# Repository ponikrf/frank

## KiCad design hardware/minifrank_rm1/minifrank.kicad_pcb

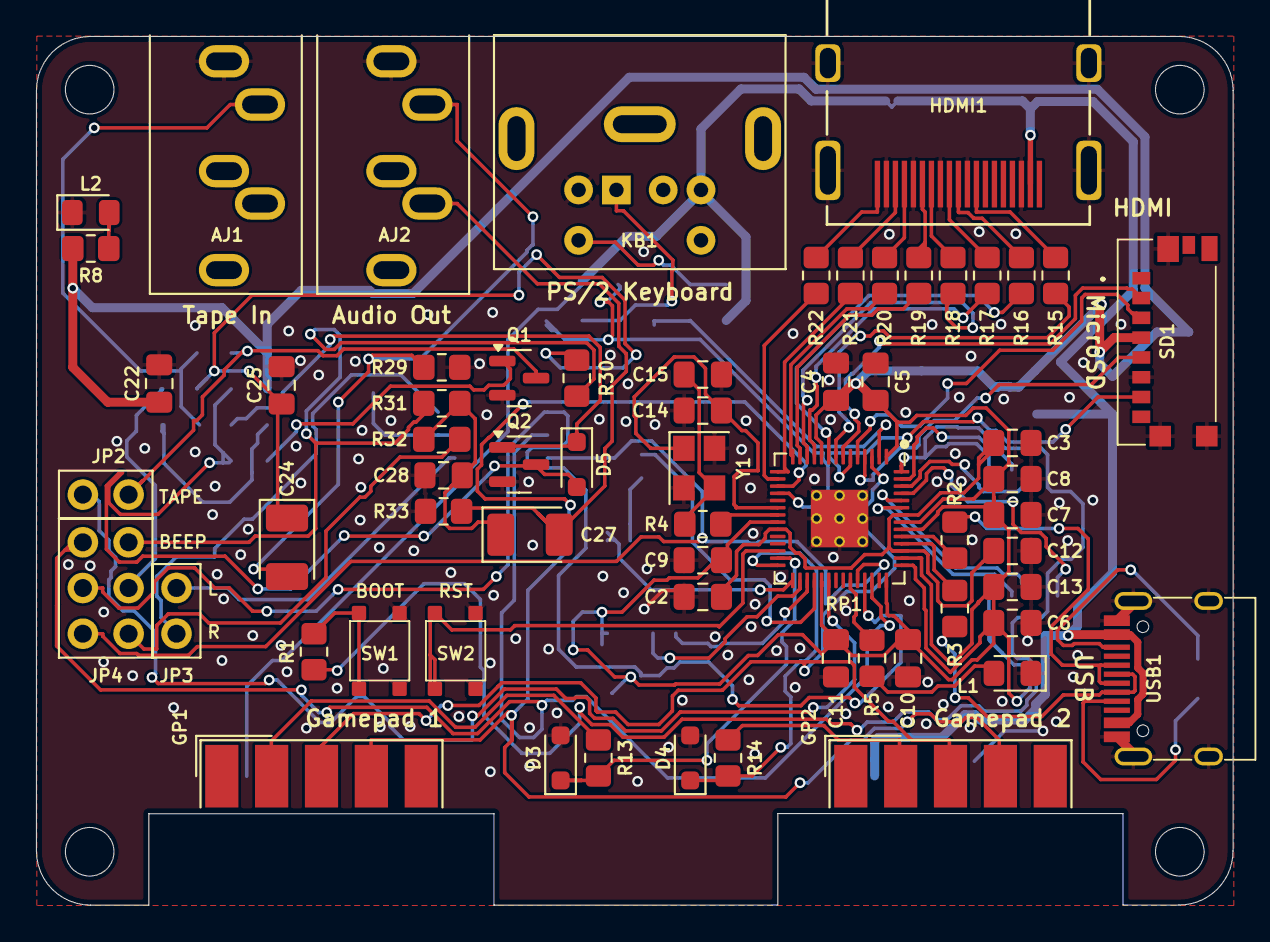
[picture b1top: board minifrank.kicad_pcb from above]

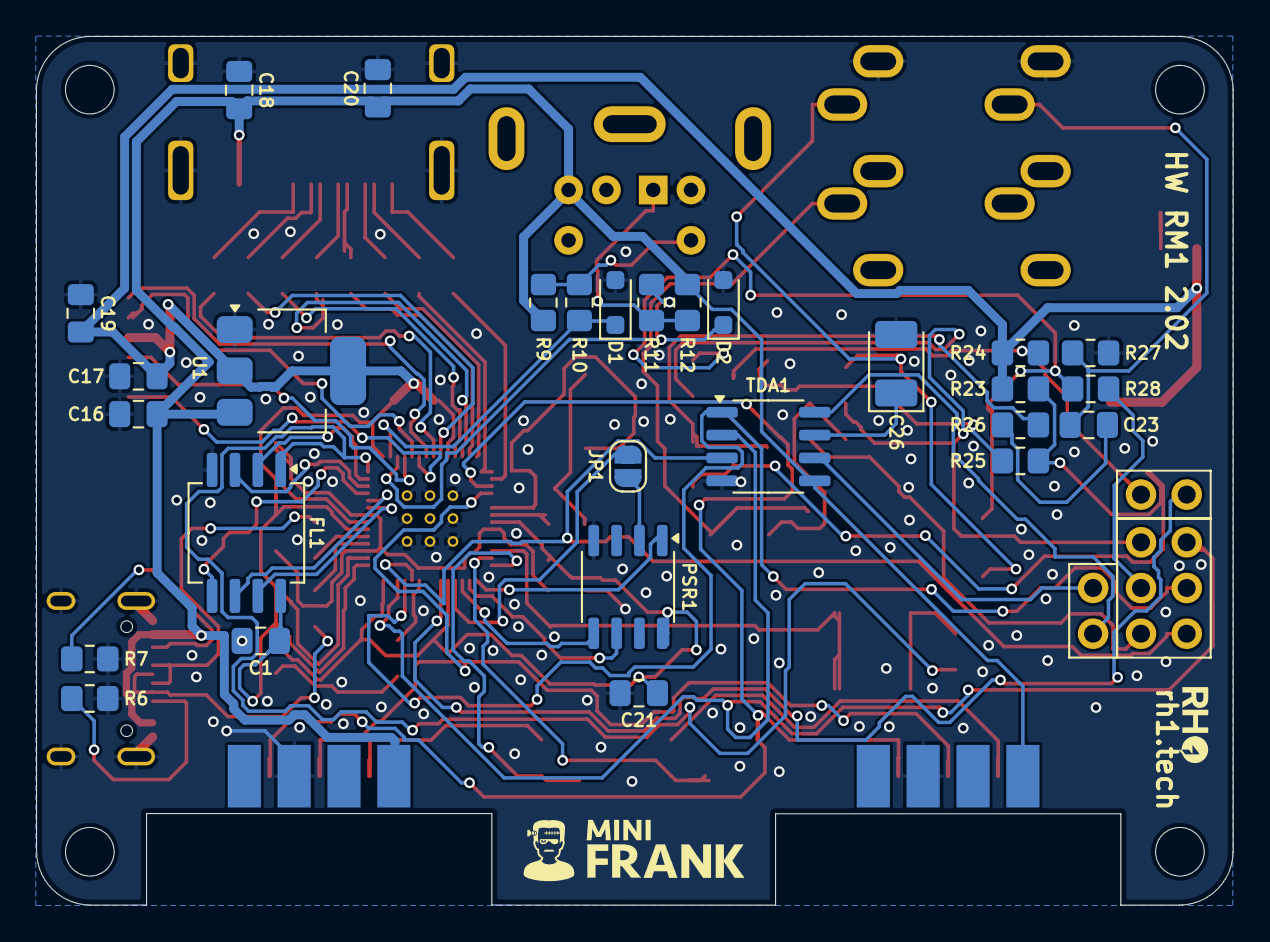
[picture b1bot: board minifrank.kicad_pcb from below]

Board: 2 copper layers, 66.5 x 48.3 mm, 94 parts (28 on the bottom side), 79 nets.

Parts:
AJ1: Audio In; Jack (3.5mm)
AJ2: Audio Out; Jack (3.5mm)
C1, C2, C3, C4, C5, C6, C7, C8, C9, C10, C11, C18, C19, C20, C21, C22, C23: 100n; Capacitor (0805)
C12, C13: 1u; Capacitor (0805)
C14, C15: 15p; Capacitor (0805)
C16, C17: 10u; Capacitor (0805)
C24, C26, C27: 10u*; Capacitor (3528, tantalum, polar)
C25, C28: 10n; Capacitor (0805)
D1, D2, D3, D4: 3V3; Diode (SOD-323)
D5: 1N4148; Diode (SOD-323)
FL1: W25Q128JVSIQ; SOIC-8
GP1, GP2: Gamepad; D-SUB (9 pin, male)
H1, H2, H3, H4: MountingHole; Mounting Hole (2.7mm)
HDMI1: HDMI Female; HDMI (female)
JP1: Jumper PSRAM (2.54); Jumper (solder)
JP2: Jumper Tape In(2.54); Pin Header (1x02)
JP3: Jumper I2S(2.54); Pin Header (1x02)
JP4: Jumpers Audio(2.54); Pin Header (2x03)
KB1: PS/2 Keyboard; MiniDIN (6 Pin, female)
L1: BLUE; LED (0805)
L2: GREEN; LED (0805)
PSR1: ESP-PSRAM32; SO-8
Q1, Q2: BC850; SOT-23
R1, R4, R5, R8, R9, R12, R13, R14, R24, R28, R32: 1K; Resistor (0805)
R2, R3: 27R; Resistor (0805)
R6, R7: 5.1K; Resistor (0805)
R10, R11, R27: 100R; Resistor (0805)
R15, R16, R17, R18, R19, R20, R21, R22: 270R; Resistor (0805)
R23, R25, R26: 10K; Resistor (0805)
R29, R33: 330R; Resistor (0805)
R30, R31: 2K; Resistor (0805)
RP1: RP2040; QFN 56
SD1: 47571-0001; MicroSD (SMD, short)
SW1: Flash Button; Button (SMD, 3x3mm)
SW2: Reset Button; Button (SMD, 3x3mm)
TDA1: TDA1387T; SO-8
U1: NCP1117 3.3; SOT-223
USB1: USB Type C
Y1: 12 MHz; Crystal (3225)

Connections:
+3V3: C1.1, C4.1, C5.1, C6.1, C7.1, C8.1, C9.1, C10.1, C11.1, C13.1, C17.1, C19.2, C21.1, C22.1, FL1.8 (VCC), PSR1.8 (VCC), R8.2, R23.1, R24.1, RP1.1 (IOVDD), RP1.10 (IOVDD), RP1.22 (IOVDD), RP1.33 (IOVDD), RP1.42 (IOVDD), RP1.43 (ADC_AVDD), RP1.44 (VREG_IN), RP1.48 (USB_VDD), RP1.49 (IOVDD), SD1.P4 (VDD), U1.2 (VO)
/AUDIO_B: JP4.6, RP1.40 (GPIO28_ADC2), TDA1.2 (LRCK)
/AUDIO_L: JP4.4, RP1.39 (GPIO27_ADC1), TDA1.1 (SCLK)
/AUDIO_R: JP4.2, RP1.38 (GPIO26_ADC0), TDA1.3 (DATA)
/Audio Out/BEEP_OUT: JP4.5, R30.2, R31.2
/Audio Out/FLT: C26.1, TDA1.7 (FLT)
/Audio Out/L: AJ2.T, C24.2, R29.1
/Audio Out/LEFT_OUT: JP4.3, R28.2
/Audio Out/LEFT_TDA: JP3.2, TDA1.6 (A_LEFT)
/Audio Out/R: AJ2.R, C27.2, R33.1
/Audio Out/RIGHT_OUT: JP4.1, R32.2
/Audio Out/RIGHT_TDA: JP3.1, TDA1.8 (A_RIGHT)
/D+: R2.1, USB1.6 (DP1), USB1.8 (DP2)
/D-: R3.1, USB1.5 (DN2), USB1.7 (DN1)
/GP1_DATA: D3.1 (K), R13.1, RP1.27 (GPIO16)
/GP2_DATA: D4.1 (K), R14.1, RP1.28 (GPIO17)
/GP_J3: GP1.3, GP2.3, RP1.18 (GPIO15)
/GP_J4: GP1.4, GP2.4, RP1.17 (GPIO14)
/HDMI_CLKN: R15.2, RP1.8 (GPIO6)
/HDMI_CLKP: R16.2, RP1.9 (GPIO7)
/HDMI_D0N: R17.2, RP1.11 (GPIO8)
/HDMI_D0P: R18.2, RP1.12 (GPIO9)
/HDMI_D1N: R19.2, RP1.13 (GPIO10)
/HDMI_D1P: R20.2, RP1.14 (GPIO11)
/HDMI_D2N: R21.2, RP1.15 (GPIO12)
/HDMI_D2P: R22.2, RP1.16 (GPIO13)
/LOAD_IN_D: JP2.2, RP1.34 (GPIO22)
/PS2_CLK: D1.1 (K), R10.2, RP1.2 (GPIO0)
/PS2_DATA: D2.1 (K), R11.2, RP1.3 (GPIO1)
/PSR_CE: PSR1.1 (~CE), RP1.29 (GPIO18)
/PSR_SCLK: PSR1.6 (SCLK), RP1.30 (GPIO19)
/PSR_SISIO: PSR1.5 (SI/SIO), RP1.31 (GPIO20)
/PSR_SOSIO: JP1.2 (B), RP1.32 (GPIO21)
/RP2040/GPIO25: R5.2, RP1.37 (GPIO25)
/RP2040/QSPI_SCLK: FL1.6 (CLK), RP1.52 (QSPI_SCLK)
/RP2040/QSPI_SD0: FL1.5 (DI(IO0)), RP1.53 (QSPI_SD0)
/RP2040/QSPI_SD1: FL1.2 (DO(IO1)), RP1.55 (QSPI_SD1)
/RP2040/QSPI_SD2: FL1.3 (IO2), RP1.54 (QSPI_SD2)
/RP2040/QSPI_SD3: FL1.7 (IO3), RP1.51 (QSPI_SD3)
/RP2040/QSPI_SS: FL1.1 (~CS), R1.1, RP1.56 (QSPI_SS)
/RP2040/XIN: C14.1, RP1.20 (XIN), Y1.1
/RP2040/XOUT: R4.1, RP1.21 (XOUT)
/RP2040/~USB_BOOT: R1.2, SW1.3, SW1.4
/RUN: RP1.26 (RUN), SW2.3, SW2.4
/SD_CLK: RP1.4 (GPIO2), SD1.P5 (CLK)
/SD_CMD: RP1.5 (GPIO3), SD1.P3 (CMD)
/SD_DAT0: RP1.6 (GPIO4), SD1.P7 (DAT0)
/SD_DAT3: RP1.7 (GPIO5), SD1.P2 (CD/DAT3)
/Tape In/LOAD_IN_D: JP2.1, Q1.3 (C), R24.2
GND: AJ1.S, AJ2.S, C1.2, C2.2, C3.2, C4.2, C5.2, C6.2, C7.2, C8.2, C9.2, C10.2, C11.2, C12.2, C13.2, C14.2, C15.2, C16.2, C17.2, C18.2, C19.1, C20.2, C21.2, C22.2, C25.2, C26.2, C28.2, D1.2 (A), D2.2 (A), D3.2 (A), D4.2 (A), FL1.4 (GND), GP1.8, GP2.8, HDMI1.2 (G_D2), HDMI1.5 (G_D1), HDMI1.8 (G_D0), HDMI1.11 (G_CLK), HDMI1.17 (G_DDC/CEC), HDMI1.20 (SHIELD1), HDMI1.21 (SHIELD2), HDMI1.22 (SHIELD3), HDMI1.23 (SHIELD4), KB1.3, L1.1 (K), L2.1 (K), PSR1.4 (VSS), Q1.2 (E), Q2.2 (E), R6.1, R7.1, R27.2, R29.2, R33.2, RP1.19 (TESTEN), RP1.57 (GND), SD1.G1 (GND_1), SD1.G2 (GND_2), SD1.G3 (GND_3), SD1.P6 (VSS), SW1.1, SW1.2, SW2.1, SW2.2, TDA1.4 (AGND), U1.1 (GND), USB1.1 (GND), USB1.12 (GND), USB1.13 (SHIELD), Y1.2, Y1.4
unnamed: AJ1.T, C23.1, R27.1
unnamed: C15.1, R4.2, Y1.3
unnamed: C23.2, R26.1
unnamed: C24.1, C25.1, R28.1, R30.1
unnamed: C27.1, C28.1, R31.1, R32.1
unnamed: D5.2 (A), Q2.3 (C), R23.2, R25.1
unnamed: D5.1 (K), Q2.1 (B), R26.2
unnamed: GP1.2, R13.2
unnamed: GP2.2, R14.2
unnamed: HDMI1.12 (CLKN), R15.1
unnamed: HDMI1.10 (CLKP), R16.1
unnamed: HDMI1.9 (D0N), R17.1
unnamed: HDMI1.7 (D0P), R18.1
unnamed: HDMI1.6 (D1N), R19.1
unnamed: HDMI1.4 (D1P), R20.1
unnamed: HDMI1.3 (D2N), R21.1
unnamed: HDMI1.1 (D2P), R22.1
unnamed: JP1.1 (A), PSR1.2 (SO/SIO)
unnamed: KB1.1, R11.1, R12.2
unnamed: KB1.5, R9.2, R10.1
unnamed: L1.2 (A), R5.1
unnamed: L2.2 (A), R8.1
unnamed: Q1.1 (B), R25.2
unnamed: R3.2, RP1.46 (USB_DM)
unnamed: R2.2, RP1.47 (USB_DP)
unnamed: C2.1, C3.1, C12.1, RP1.23 (DVDD), RP1.45 (VREG_VOUT), RP1.50 (DVDD)
unnamed: R6.2, USB1.4 (CC1)
unnamed: R7.2, USB1.10 (CC2)
VBUS: C16.1, C18.1, C20.1, GP1.6, GP2.6, HDMI1.18 (+5V), KB1.4, R9.1, R12.1, TDA1.5 (VA), U1.3 (VI), USB1.2 (VBUS), USB1.11 (VBUS)

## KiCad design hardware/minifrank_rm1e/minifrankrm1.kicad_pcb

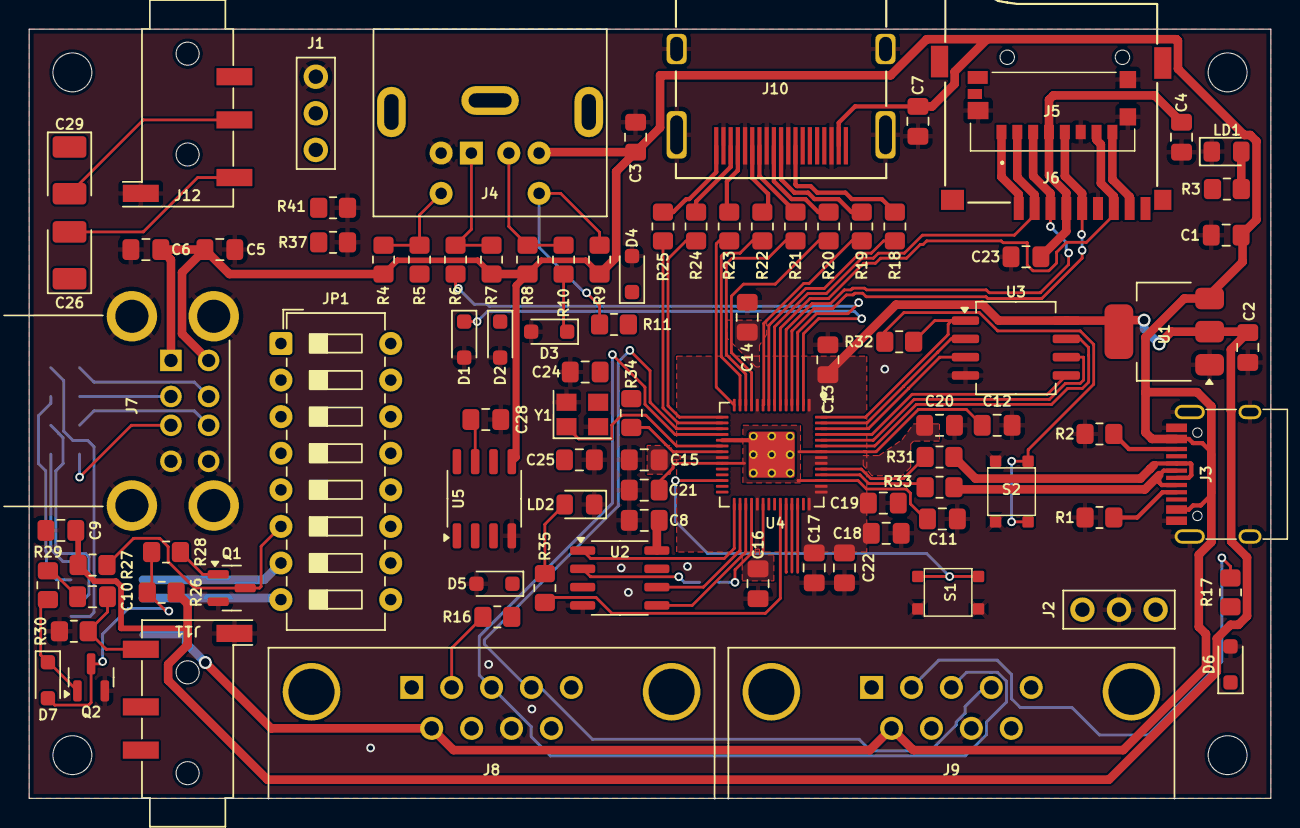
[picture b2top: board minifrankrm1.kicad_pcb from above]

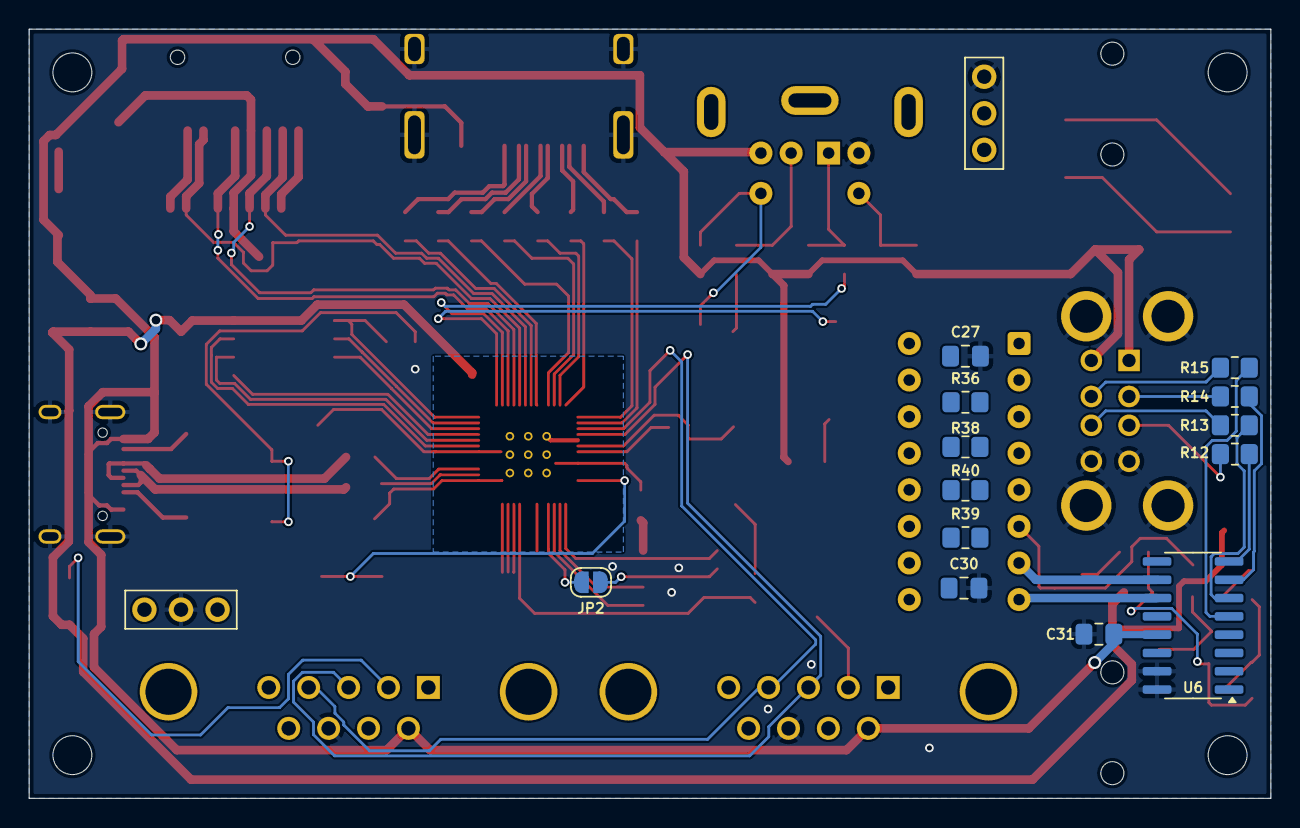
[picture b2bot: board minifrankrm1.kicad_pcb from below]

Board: 2 copper layers, 86.2 x 53.4 mm, 110 parts (13 on the bottom side), 96 nets.

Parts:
C1, C2, C5, C6, C28: 10u; Capacitor (0805)
C3, C4, C7, C8, C9, C10, C11, C12, C13, C14, C15, C16, C17, C18, C19, C20, C23: 100n; Capacitor (0805)
C21, C22: 1u; Capacitor (0805)
C24, C25: 15p; Capacitor (0805)
C26, C29: 10u; Capacitor (3528, tantalum, polar)
C27, C30: 10n; Capacitor (0805)
C31: 4.7u; Capacitor (0805)
D1, D2, D3, D4, D5, D6: 3V3; Diode (SOD-323)
D7: 1N4148; Diode (SOD-323)
H1, H2, H3, H4: Hole 2.7mm; Mounting Hole (2.7mm)
J1: UART; Pin Header (1x03)
J2: Power; Pin Header (1x03)
J3: USB4215; USB Type C
J4: MDC-036; MiniDIN (6 Pin, female)
J5: 0475710001; MicroSD (SMD, short)
J6: 104031-0811; MicroSD (SMD, long)
J7: SS-52100-004; USB Type A (stacked)
J8, J9: D-SUB 9 Male; D-SUB (9 pin, male, top mount)
J10: DC3RX19JA2; HDMI (female)
J11, J12: PJ-320D; Jack (3.5mm, PJ-320D)
JP1: Main Jumpers; DIP Switch (8x8)
JP2: Jumper (Solder); Jumper (solder)
LD1: Green; LED (0805)
LD2: Blue; LED (0805)
Q1, Q2: BC850; SOT-23
R1, R2: 5.1K; Resistor (0805)
R3, R4, R7, R8, R9, R16, R17, R27, R32, R34, R35, R36, R40: 1K; Resistor (0805)
R5, R6, R10, R11, R30: 100R; Resistor (0805)
R12, R13, R14, R15: 22R; Resistor (0805)
R18, R19, R20, R21, R22, R23, R24, R25: 270R; Resistor (0805)
R26, R28, R29: 10K; Resistor (0805)
R31, R33: 27R; Resistor (0805)
R37, R41: 330R; Resistor (0805)
R38, R39: 2K; Resistor (0805)
S1, S2: TS-1233; Button (SMD, 3x3mm, 1-1)
U1: NCP1117 3.3; SOT-223
U2: ESP-PSRAM32; SO-8
U3: W25Q128JVSIQ; SOIC-8
U4: RP2040; QFN 56
U5: TDA1387T; SO-8
U6: MW7211A; SOP-16
Y1: 12 MHz; Crystal (3225)

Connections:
+3V3: C2.1, C4.2, C8.1, C9.1, C13.1, C14.1, C15.1, C16.1, C17.1, C18.1, C19.1, C20.1, C22.1, C23.1, J2.1, J5.P4 (VDD), J6.4 (VDD), R3.2, R26.1, R27.1, U1.2 (VO), U2.8 (VCC), U3.8 (VCC), U4.1 (IOVDD), U4.10 (IOVDD), U4.22 (IOVDD), U4.33 (IOVDD), U4.42 (IOVDD), U4.43 (ADC_AVDD), U4.44 (VREG_IN), U4.48 (USB_VDD), U4.49 (IOVDD)
/Audio/L: C26.2, J12.T, R37.1
/Audio/R: C29.2, J12.R, R41.1
/GP1_DATA: D5.1 (K), R16.1
/GP2_DATA: D6.1 (K), R17.1
/GPIO0: D1.1 (K), J1.2, R5.2, U4.2 (GPIO0)
/GPIO1: D2.1 (K), J1.3, R6.2, U4.3 (GPIO1)
/GPIO2: J5.P5 (CLK), J6.5 (CLK), U4.4 (GPIO2)
/GPIO3: J5.P3 (CMD), J6.3 (CMD), U4.5 (GPIO3)
/GPIO4: J5.P7 (DAT0), J6.7 (DAT0), U4.6 (GPIO4)
/GPIO5: J5.P2 (CD/DAT3), J6.2 (DAT3/CD), U4.7 (GPIO5)
/GPIO6: R18.2, U4.8 (GPIO6)
/GPIO7: R19.2, U4.9 (GPIO7)
/GPIO8: R20.2, U4.11 (GPIO8)
/GPIO9: R21.2, U4.12 (GPIO9)
/GPIO10: R22.2, U4.13 (GPIO10)
/GPIO11: R23.2, U4.14 (GPIO11)
/GPIO12: R24.2, U4.15 (GPIO12)
/GPIO13: R25.2, U4.16 (GPIO13)
/GPIO14: J8.4, J9.4, U4.17 (GPIO14)
/GPIO15: J8.3, J9.3, U4.18 (GPIO15)
/GPIO18: U2.1 (~CE), U4.29 (GPIO18)
/GPIO19: U2.6 (SCLK), U4.30 (GPIO19)
/GPIO20: U2.5 (SI/SIO), U4.31 (GPIO20)
/GPIO21: JP2.2 (B), U4.32 (GPIO21)
/GPIO22: JP1.12, U4.34 (GPIO22)
/GPIO26: JP1.4, U4.38 (GPIO26_ADC0), U5.3 (DATA)
/GPIO27: JP1.2, U4.39 (GPIO27_ADC1), U5.1 (SCLK)
/GPIO28: JP1.10, U4.40 (GPIO28_ADC2), U5.2 (LRCK)
/KB_CLK: J4.5, R4.2, R5.1
/KB_DATA: J4.1, R6.1, R7.2
/LOAD_IN_D: JP1.11, Q1.3 (C), R27.2
/MS_CLK: J4.6, R9.2, R11.1
/MS_CLK_3V: D4.1 (K), R11.2
/MS_DATA: J4.2, R8.2, R10.1
/MS_DATA_3V: D3.1 (K), R10.2
/Micro SD/DAT1: J5.P8 (DAT1), J6.8 (DAT1)
/Micro SD/DAT2: J5.P1 (DAT2), J6.1 (DAT2)
/OUT_B: JP1.9, R38.2, R39.2
/OUT_L: JP1.1, JP1.6, R36.2
/OUT_R: JP1.3, JP1.8, R40.2
/PW_DM: J3.5 (DN2), J3.7 (DN1), JP1.14, R33.1
/PW_DP: J3.6 (DP1), J3.8 (DP2), JP1.16, R31.1
/RP2040/GPIO25: R35.2, U4.37 (GPIO25)
/RP2040/QSPI_SCLK: U3.6 (CLK), U4.52 (QSPI_SCLK)
/RP2040/QSPI_SD0: U3.5 (DI(IO0)), U4.53 (QSPI_SD0)
/RP2040/QSPI_SD1: U3.2 (DO(IO1)), U4.55 (QSPI_SD1)
/RP2040/QSPI_SD2: U3.3 (IO2), U4.54 (QSPI_SD2)
/RP2040/QSPI_SD3: U3.7 (IO3), U4.51 (QSPI_SD3)
/RP2040/QSPI_SS: R32.1, U3.1 (~CS), U4.56 (QSPI_SS)
/RP2040/XIN: C25.1, U4.20 (XIN), Y1.1
/RP2040/XOUT: R34.1, U4.21 (XOUT)
/RP2040/~USB_BOOT: R32.2, S2.2
/RUN: S1.1, U4.26 (RUN)
/TDA_L: JP1.5, U5.6 (A_LEFT)
/TDA_R: JP1.7, U5.8 (A_RIGHT)
/UH_DM1: R14.1, U6.7 (DM3)
/UH_DM2: R15.1, U6.5 (DM2)
/UH_DM_IN: JP1.13, U6.10 (DMU)
/UH_DP1: R12.1, U6.8 (DP3)
/UH_DP2: R13.1, U6.6 (DP2)
/UH_DP_IN: JP1.15, U6.11 (DPU)
GND: C1.2, C2.2, C3.2, C4.1, C5.2, C6.2, C7.2, C8.2, C9.2, C11.2, C12.2, C13.2, C14.2, C15.2, C16.2, C17.2, C18.2, C19.2, C20.2, C21.2, C22.2, C23.2, C24.2, C25.2, C27.2, C28.2, C30.2, C31.2, D1.2 (A), D2.2 (A), D3.2 (A), D4.2 (A), D5.2 (A), D6.2 (A), J1.1, J2.2, J3.1 (GND), J3.12 (GND), J3.13 (SHIELD), J4.3, J5.G1 (GND_1), J5.G2 (GND_2), J5.G3 (GND_3), J5.P6 (VSS), J6.6 (VSS), J7.4 (GND1), J7.8 (GND2), J7.9 (Shield), J8.8, J9.8, J10.2 (G_D2), J10.5 (G_D1), J10.8 (G_D0), J10.11 (G_CLK), J10.17 (G_DDC/CEC), J10.20 (SHIELD1), J10.21 (SHIELD2), J10.22 (SHIELD3), J10.23 (SHIELD4), J11.S, J12.S, LD1.1 (K), LD2.1 (K), Q1.2 (E), Q2.2 (E), R1.1, R2.1, R30.2, R37.2, R41.2, S1.2, S2.1, U1.1 (GND), U2.4 (VSS), U3.4 (GND), U4.19 (TESTEN), U4.57 (GND), U5.4 (AGND), U6.15 (GND), U6.16 (GND), Y1.2, Y1.4
unnamed: C10.1, J11.T, R30.1
unnamed: C10.2, R29.1
unnamed: C24.1, R34.2, Y1.3
unnamed: C26.1, C27.1, R36.1, R38.1
unnamed: C29.1, C30.1, R39.1, R40.1
unnamed: D7.2 (A), Q2.3 (C), R26.2, R28.1
unnamed: D7.1 (K), Q2.1 (B), R29.2
unnamed: J3.4 (CC1), R1.2
unnamed: J3.10 (CC2), R2.2
unnamed: J7.3 (D1+), R12.2
unnamed: J7.2 (D1-), R14.2
unnamed: J7.7 (D2+), R13.2
unnamed: J7.6 (D2-), R15.2
unnamed: J8.2, R16.2
unnamed: J9.2, R17.2
unnamed: J10.12 (CLKN), R18.1
unnamed: J10.10 (CLKP), R19.1
unnamed: J10.9 (D0N), R20.1
unnamed: J10.7 (D0P), R21.1
unnamed: J10.6 (D1N), R22.1
unnamed: J10.4 (D1P), R23.1
unnamed: J10.3 (D2N), R24.1
unnamed: J10.1 (D2P), R25.1
unnamed: JP2.1 (A), U2.2 (SO/SIO)
unnamed: LD1.2 (A), R3.1
unnamed: LD2.2 (A), R35.1
unnamed: Q1.1 (B), R28.2
unnamed: R33.2, U4.46 (USB_DM)
unnamed: R31.2, U4.47 (USB_DP)
unnamed: C11.1, C12.1, C21.1, U4.23 (DVDD), U4.45 (VREG_VOUT), U4.50 (DVDD)
unnamed: C28.1, U5.7 (FLT)
unnamed: U6.12 (VD33), U6.14 (VD3)
VBUS: C1.1, C3.1, C5.1, C6.1, C7.1, C31.1, J2.3, J3.2 (VBUS), J3.11 (VBUS), J4.4, J7.1 (VBUS1), J7.5 (VBUS2), J8.6, J9.6, J10.18 (+5V), R4.1, R7.1, R8.1, R9.1, U1.3 (VI), U5.5 (VA), U6.13 (VDD5)

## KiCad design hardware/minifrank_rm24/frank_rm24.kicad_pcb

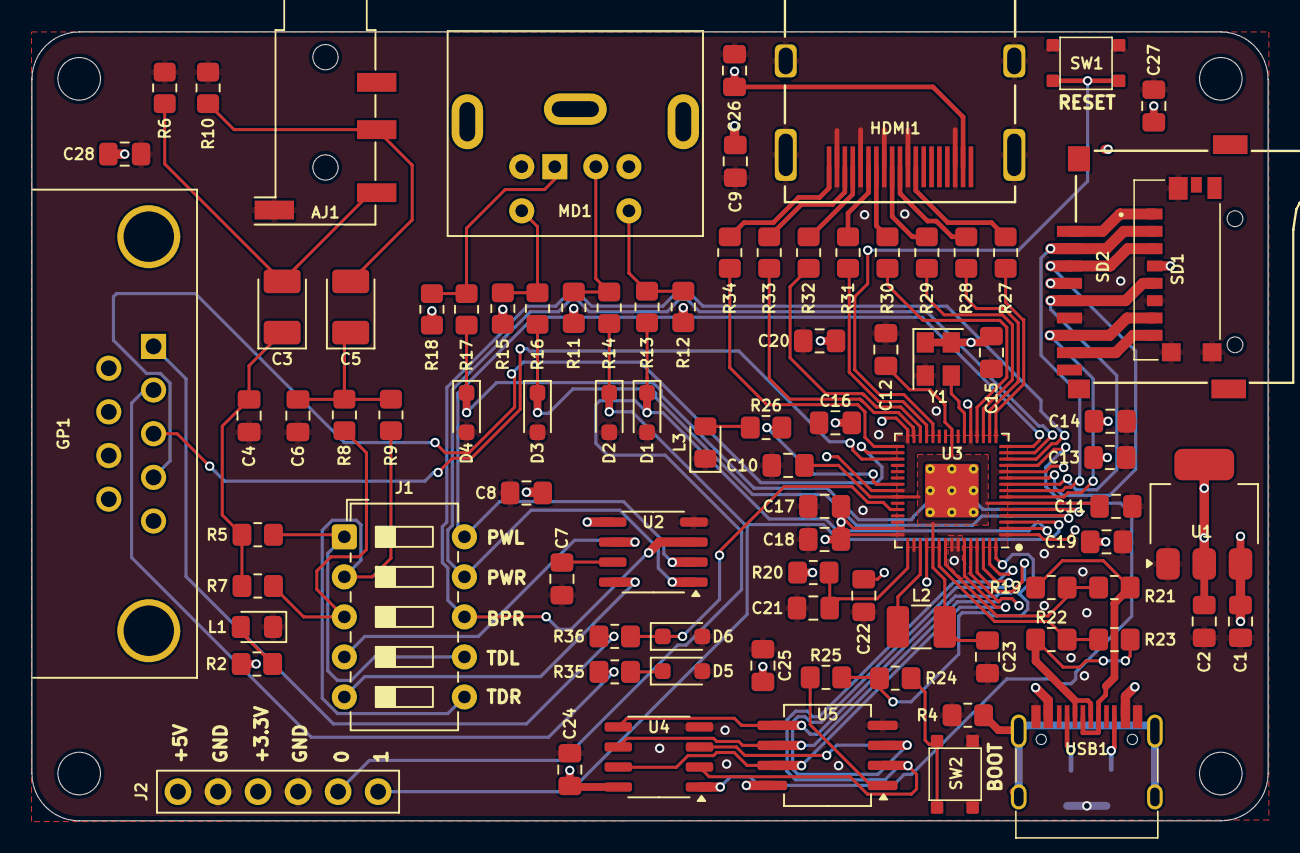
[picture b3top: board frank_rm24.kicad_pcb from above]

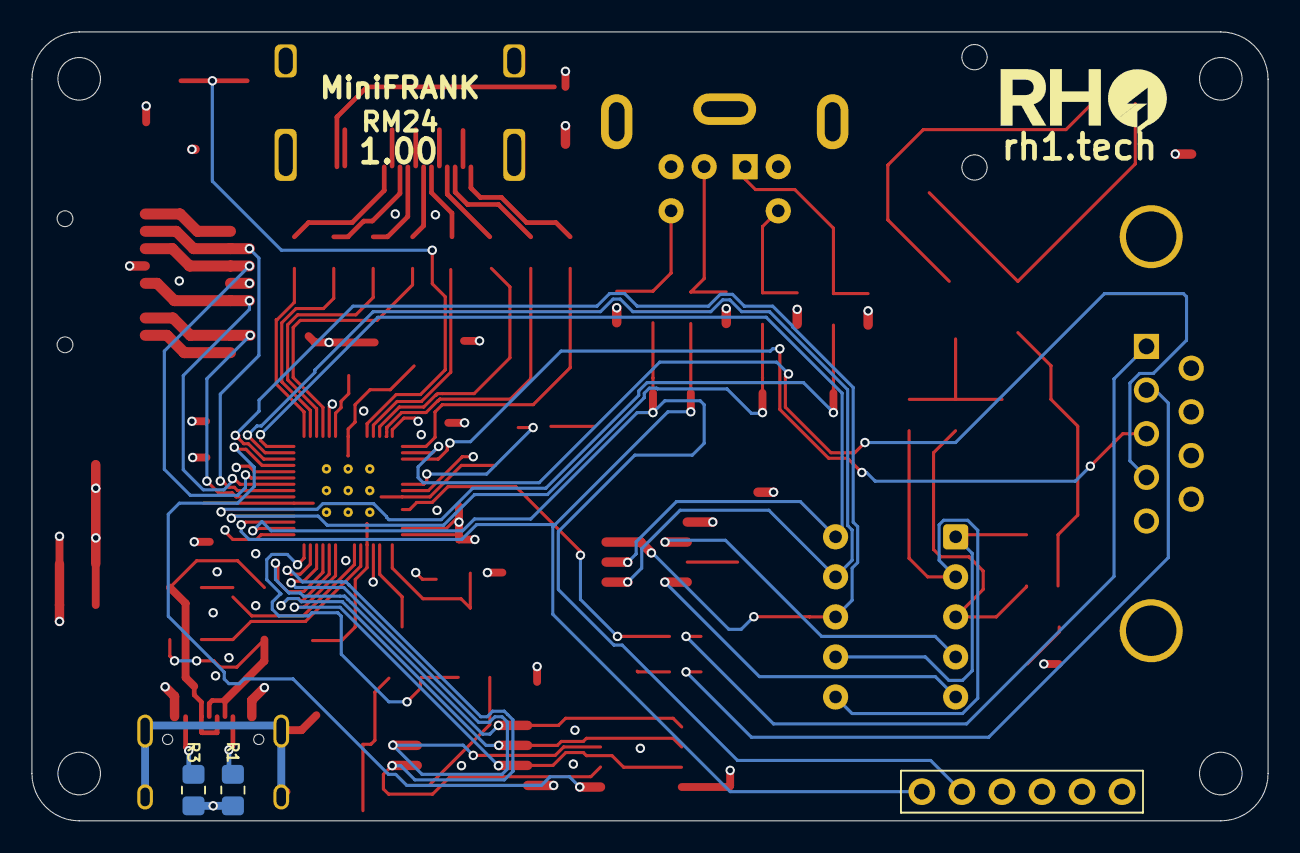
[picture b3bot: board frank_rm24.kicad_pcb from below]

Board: 4 copper layers, 78.4 x 50.0 mm, 94 parts (2 on the bottom side), 76 nets.

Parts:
AJ1: PJ-320D; Jack (3.5mm, PJ-320D)
C1, C2, C9: 10u; Capacitor (0805)
C3, C5: 10u; Capacitor (3528, tantalum, polar)
C4, C6: 10n; Capacitor (0805)
C7: 1u; Capacitor (0805)
C8: 47u; Capacitor (0805)
C10, C12, C13, C14, C15, C16, C17, C18, C19, C20, C24, C25, C26, C27, C28: 100n; Capacitor (0805)
C11, C21, C22, C23: 4.7u; Capacitor (0805)
D1, D2, D3, D4, D5, D6: 3V3; Diode (SOD-323)
GP1: Gamepad; D-SUB (9 pin, male, top mount)
H1, H2, H3, H4: MountingHole; Mounting Hole (2.7mm)
HDMI1: HDMI Female; HDMI (female)
J1: Pin Header 2x18; DIP Switch (5x5)
J2: Connectors; Pin Header (1x06)
L1: Green; LED (0805)
L2: 3.3u; Inductor (3225)
L3: Blue; LED (0805)
MD1: Mini-DIN-6; MiniDIN (6 Pin, female)
R1, R3: 5.1K; Resistor (0805)
R2, R5, R9, R11, R12, R15, R24, R26, R35, R36: 1K; Resistor (0805)
R4: 1M; Resistor (0805)
R6, R10: 330R; Resistor (0805)
R7, R8: 2K; Resistor (0805)
R13, R14, R16, R17: 100R; Resistor (0805)
R18: 1k; Resistor (0805)
R19, R22: 150R; Resistor (0805)
R20: 33; Resistor (0805)
R21, R23: 33R; Resistor (0805)
R25: 0; Resistor (0805)
R27, R28, R29, R30, R31, R32, R33, R34: 270R; Resistor (0805)
SD1: 47571-0001; MicroSD (SMD, short)
SD2: 104031-0811; MicroSD (SMD, long)
SW1: Reset; Button (SMD, 3x3mm, 1-1)
SW2: SW_Push; Button (SMD, 3x3mm, 1-1)
U1: NCP1117 3.3; SOT-223
U2: TDA1387T; SO-8
U3: RP2350_60QFN; QFN 60 (RP2350A)
U4: ESP-PSRAM32; SO-8
U5: W25Q128JVS; SOIC-8
USB1: USB4215-03-A; USB Type C
Y1: ASE-xxxMHz; Crystal (3225, active)

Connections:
+1V1: C10.1, C11.1, C12.1, C23.1, L2.1, U3.6 (DVDD), U3.23 (DVDD), U3.39 (DVDD), U3.50 (VREG_FB)
+3V3: C2.1, C13.1, C14.1, C15.1, C16.1, C17.1, C18.1, C19.1, C20.1, C22.1, C24.1, C25.1, C27.2, J2.3, R2.2, R20.1, SD1.P4 (VDD), SD2.4 (VDD), U1.2 (VO), U3.1 (IOVDD), U3.11 (IOVDD), U3.20 (IOVDD), U3.30 (IOVDD), U3.38 (IOVDD), U3.44 (ADC_AVDD), U3.45 (IOVDD), U3.49 (VREG_VIN), U3.53 (USB_OTP_VDD), U3.54 (QSPI_IOVDD), U4.8 (VCC), U5.8 (VCC), Y1.1 (EN), Y1.4 (Vdd)
/A_OUTB: J1.5, R7.2, R8.2
/A_OUTL: J1.1, J1.8, R5.2
/A_OUTR: J1.3, J1.10, R9.2
/A_TDAL: J1.7, U2.6 (A_LEFT)
/A_TDAR: J1.9, U2.8 (A_RIGHT)
/Audio Out/L: AJ1.T, C3.2, R6.1
/Audio Out/R: AJ1.R, C5.2, R10.1
/D+: R19.1, R21.1, USB1.6 (DP1), USB1.8 (DP2)
/D-: R22.1, R23.1, USB1.5 (DN2), USB1.7 (DN1)
/GPIO0: D1.1 (K), J2.5, R13.2, U3.2 (GPIO0)
/GPIO1: D2.1 (K), J2.6, R14.2, U3.3 (GPIO1)
/GPIO2: D3.1 (K), R16.2, U3.4 (GPIO2)
/GPIO3: D4.1 (K), R17.2, U3.5 (GPIO3)
/GPIO4: SD1.P7 (DAT0), SD2.7 (DAT0), U3.7 (GPIO4)
/GPIO5: SD1.P2 (CD/DAT3), SD2.2 (DAT3/CD), U3.8 (GPIO5)
/GPIO6: SD1.P5 (CLK), SD2.5 (CLK), U3.9 (GPIO6)
/GPIO7: SD1.P3 (CMD), SD2.3 (CMD), U3.10 (GPIO7)
/GPIO8: U3.12 (GPIO8), U4.1 (~CE)
/GPIO9: J1.6, U2.3 (DATA), U3.13 (GPIO9)
/GPIO10: J1.4, U2.1 (SCLK), U3.14 (GPIO10)
/GPIO11: J1.2, U2.2 (LRCK), U3.15 (GPIO11)
/GPIO12: R27.2, U3.16 (GPIO12)
/GPIO13: R28.2, U3.17 (GPIO13)
/GPIO14: R29.2, U3.18 (GPIO14)
/GPIO15: R30.2, U3.19 (GPIO15)
/GPIO16: R31.2, U3.27 (GPIO16)
/GPIO17: R32.2, U3.28 (GPIO17)
/GPIO18: R33.2, U3.29 (GPIO18)
/GPIO19: R34.2, U3.31 (GPIO19)
/GPIO20: GP1.4, U3.32 (GPIO20)
/GPIO21: GP1.3, U3.33 (GPIO21)
/GPIO26: D5.1 (K), R35.1
/GPIO27: D6.1 (K), R36.1, U3.41 (GPIO27_ADC1)
/Gamepad/J1_DATA: GP1.2, R35.2
/Gamepad/J2_DATA: GP1.1, R36.2
/PS2/PS/2 CLK: MD1.5, R15.2, R16.1
/PS2/PS/2 DATA: MD1.1, R17.1, R18.2
/RP2350A/FLASH_SS: R25.2, U5.1 (~CS)
/RP2350A/QSPI_SCLK: U3.56 (QSPI_SCLK), U4.6 (SCLK), U5.6 (CLK)
/RP2350A/QSPI_SD0: U3.57 (QSPI_SD0), U4.5 (SI/SIO), U5.5 (DI(IO0))
/RP2350A/QSPI_SD1: U3.59 (QSPI_SD1), U4.2 (SO/SIO), U5.2 (DO(IO1))
/RP2350A/QSPI_SD2: U3.58 (QSPI_SD2), U4.3 (SIO2), U5.3 (IO2)
/RP2350A/QSPI_SD3: U3.55 (QSPI_SD3), U4.7 (SIO3), U5.7 (IO3)
/RP2350A/QSPI_SS: R24.1, R25.1, U3.60 (QSPI_SS)
/RP2350A/VREG_AVDD: C21.1, R20.2, U3.46 (VREG_AVDD)
/RP2350A/VREG_LX: L2.2, U3.48 (VREG_LX)
/RP2350A/XIN: U3.21 (XIN), Y1.3 (OUT)
/RP2350A/~USB_BOOT: R24.2, SW2.2
/RUN: SW1.1, U3.26 (RUN)
/SD Card/DAT1: SD1.P8 (DAT1), SD2.8 (DAT1)
/SD Card/DAT2: SD1.P1 (DAT2), SD2.1 (DAT2)
GND: AJ1.S, C1.2, C2.2, C4.2, C6.2, C7.2, C8.1, C9.2, C10.2, C11.2, C12.2, C13.2, C14.2, C15.2, C16.2, C17.2, C18.2, C19.2, C20.2, C21.2, C22.2, C23.2, C24.2, C25.2, C26.2, C27.1, C28.2, D1.2 (A), D2.2 (A), D3.2 (A), D4.2 (A), D5.2 (A), D6.2 (A), GP1.8, HDMI1.2 (G_D2), HDMI1.5 (G_D1), HDMI1.8 (G_D0), HDMI1.11 (G_CLK), HDMI1.17 (G_DDC/CEC), HDMI1.20 (SHIELD1), HDMI1.21 (SHIELD2), HDMI1.22 (SHIELD3), HDMI1.23 (SHIELD4), J2.2, J2.4, L1.1 (K), L3.1 (K), MD1.3, R1.1, R3.1, R4.2, R6.2, R10.2, SD1.G1 (GND_1), SD1.G2 (GND_2), SD1.G3 (GND_3), SD1.P6 (VSS), SD2.6 (VSS), SW1.2, SW2.1, U1.1 (GND), U2.4 (AGND), U3.47 (VREG_PGND), U3.61 (GND), U4.4 (VSS), U5.4 (GND), USB1.1 (GND), USB1.12 (GND), Y1.2 (GND)
GPIO25: R26.2, U3.37 (GPIO25)
unnamed: C3.1, C4.1, R5.1, R7.1
unnamed: C5.1, C6.1, R8.1, R9.1
unnamed: HDMI1.12 (CLKN), R27.1
unnamed: HDMI1.10 (CLKP), R28.1
unnamed: HDMI1.9 (D0N), R29.1
unnamed: HDMI1.7 (D0P), R30.1
unnamed: HDMI1.6 (D1N), R31.1
unnamed: HDMI1.4 (D1P), R32.1
unnamed: HDMI1.3 (D2N), R33.1
unnamed: HDMI1.1 (D2P), R34.1
unnamed: L1.2 (A), R2.1
unnamed: L3.2 (A), R26.1
unnamed: MD1.2, R11.2, R14.1
unnamed: MD1.6, R12.2, R13.1
unnamed: C7.1, U2.7 (FLT)
unnamed: R22.2, R23.2, U3.51 (USB_DM)
unnamed: R19.2, R21.2, U3.52 (USB_DP)
unnamed: R1.2, USB1.4 (CC1)
unnamed: R3.2, USB1.10 (CC2)
unnamed: R4.1, USB1.13 (SHIELD)
VBUS: C1.1, C8.2, C9.1, C26.1, C28.1, GP1.6, HDMI1.18 (+5V), J2.1, MD1.4, R11.1, R12.1, R15.1, R18.1, U1.3 (VI), U2.5 (VA), USB1.2 (VBUS), USB1.11 (VBUS)

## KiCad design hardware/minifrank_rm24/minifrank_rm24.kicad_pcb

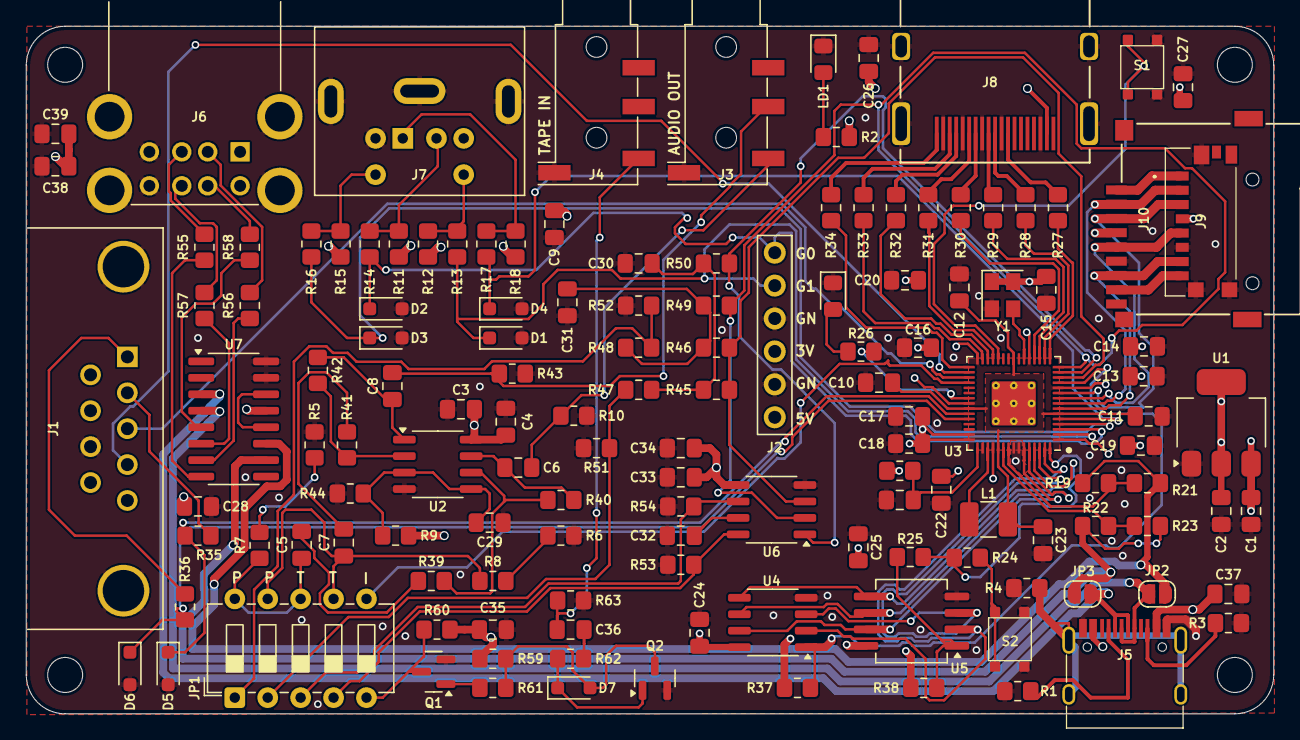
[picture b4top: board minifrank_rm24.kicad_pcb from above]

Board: 4 copper layers, 96.2 x 53.0 mm, 141 parts (0 on the bottom side), 104 nets.

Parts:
C1, C2, C3, C5, C6, C7, C8, C9, C29, C32, C33, C38, C39: 10u; Capacitor (0805)
C4, C10, C12, C13, C14, C15, C16, C17, C18, C19, C20, C24, C25, C26, C27, C28, C34, C35, C36: 100n; Capacitor (0805)
C11, C21, C22, C23, C37: 4.7u; Capacitor (0805)
C30, C31: 47n; Capacitor (0805)
D1, D2, D3, D4, D5, D6: 3V3; Diode (SOD-323)
D7: 1N4148; Diode (SOD-323)
H1, H2, H3, H4: MountingHole; Mounting Hole (2.7mm)
J1: Gamepad; D-SUB (9 pin, male, top mount)
J2: Connectors; Pin Header (1x06)
J3, J4: PJ-320D; Jack (3.5mm, PJ-320D)
J5: USB4215-03-A; USB Type C
J6: SS-52100-004; USB Type A (stacked)
J7: Mini-DIN-6; MiniDIN (6 Pin, female)
J8: HDMI Female; HDMI (female)
J9: 47571-0001; MicroSD (SMD, short)
J10: 104031-0811; MicroSD (SMD, long)
JP1: SD04H0SB; DIP Switch (5x5)
JP2, JP3: Jumper (Solder); Jumper (solder)
L1: 3.3u; Inductor (3225)
LD1: Green; LED (0805)
LD2: Blue; LED (0805)
Q1, Q2: BC850; SOT-23
R1, R3: 5.1K; Resistor (0805)
R2, R11, R12, R15, R24, R26, R35, R36, R49, R50, R60: 1K; Resistor (0805)
R4: 1M; Resistor (0805)
R5, R6, R45, R46, R51, R52: 2K; Resistor (0805)
R7, R8, R9, R37, R38, R39, R41, R44, R47, R48, R59, R61, R62: 10K; Resistor (0805)
R10, R43: 20K; Resistor (0805)
R13, R14, R16, R17, R63: 100R; Resistor (0805)
R18: 1k; Resistor (0805)
R19, R22: 150R; Resistor (0805)
R20: 33; Resistor (0805)
R21, R23: 33R; Resistor (0805)
R25: 0; Resistor (0805)
R27, R28, R29, R30, R31, R32, R33, R34: 270R; Resistor (0805)
R40, R42: 47K; Resistor (0805)
R53, R54: 470R; Resistor (0805)
R55, R56, R57, R58: 22R; Resistor (0805)
S1, S2: TS-1233; Button (SMD, 3x3mm, 1-1)
U1: NCP1117 3.3; SOT-223
U2: LM358; SO-8
U3: RP2350; QFN 60 (RP2350A)
U4: ESP-PSRAM32; SO-8
U5: W25Q128JVS; SOIC-8
U6: TDA1387T; SO-8
U7: MW7211A; SOP-16
Y1: ASE-12MHz; Crystal (3225, active)

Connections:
+1V1: C10.1, C11.1, C12.1, C23.1, L1.1, U3.6 (DVDD), U3.23 (DVDD), U3.39 (DVDD), U3.50 (VREG_FB)
+3V3: C2.1, C13.1, C14.1, C15.1, C16.1, C17.1, C18.1, C19.1, C20.1, C22.1, C24.1, C25.1, C27.2, C35.1, J2.3, J9.P4 (VDD), J10.4 (VDD), R2.2, R20.1, R37.2, R38.1, R59.1, R60.1, U1.2 (VO), U3.1 (IOVDD), U3.11 (IOVDD), U3.20 (IOVDD), U3.30 (IOVDD), U3.38 (IOVDD), U3.44 (ADC_AVDD), U3.45 (IOVDD), U3.49 (VREG_VIN), U3.53 (USB_OTP_VDD), U3.54 (QSPI_IOVDD), U4.8 (VCC), U5.8 (VCC), Y1.1 (EN), Y1.4 (Vdd)
/AMP_OUTL: C5.1, JP1.2, JP1.6, R7.1
/AMP_OUTR: C7.1, JP1.4, JP1.8, R8.1
/Audio Out/AMP_OUTL: C6.2, J3.T, R10.2
/Audio Out/AMP_OUTR: C8.2, J3.R, R43.2
/D+: JP2.2 (B), R19.1, R21.1, U7.11 (DPU)
/D-: JP3.2 (B), R22.1, R23.1, U7.10 (DMU)
/GPIO0: D1.1 (K), J2.5, R13.2, U3.2 (GPIO0)
/GPIO1: D2.1 (K), J2.6, R14.2, U3.3 (GPIO1)
/GPIO2: D3.1 (K), R16.2, U3.4 (GPIO2)
/GPIO3: D4.1 (K), R17.2, U3.5 (GPIO3)
/GPIO4: J9.P7 (DAT0), J10.7 (DAT0), U3.7 (GPIO4)
/GPIO5: J9.P2 (CD/DAT3), J10.2 (DAT3/CD), U3.8 (GPIO5)
/GPIO6: J9.P5 (CLK), J10.5 (CLK), U3.9 (GPIO6)
/GPIO7: J9.P3 (CMD), J10.3 (CMD), U3.10 (GPIO7)
/GPIO8: R37.1, U3.12 (GPIO8), U4.1 (~CE)
/GPIO9: R45.1, R46.1, U3.13 (GPIO9), U6.3 (DATA)
/GPIO10: R50.2, U3.14 (GPIO10), U6.1 (SCLK)
/GPIO11: R49.2, U3.15 (GPIO11), U6.2 (LRCK)
/GPIO12: R27.2, U3.16 (GPIO12)
/GPIO13: R28.2, U3.17 (GPIO13)
/GPIO14: R29.2, U3.18 (GPIO14)
/GPIO15: R30.2, U3.19 (GPIO15)
/GPIO16: R31.2, U3.27 (GPIO16)
/GPIO17: R32.2, U3.28 (GPIO17)
/GPIO18: R33.2, U3.29 (GPIO18)
/GPIO19: R34.2, U3.31 (GPIO19)
/GPIO20: J1.4, U3.32 (GPIO20)
/GPIO21: J1.3, U3.33 (GPIO21)
/GPIO22: JP1.10, U3.34 (GPIO22)
/GPIO26: D5.1 (K), R35.1, U3.40 (GPIO26_ADC0)
/GPIO27: D6.1 (K), R36.1, U3.41 (GPIO27_ADC1)
/Gamepad/J1_DATA: J1.2, R35.2
/Gamepad/J2_DATA: J1.1, R36.2
/LOAD_IN: JP1.9, Q1.3 (C), R60.2
/PS2/PS/2 CLK: J7.5, R15.2, R16.1
/PS2/PS/2 DATA: J7.1, R17.1, R18.2
/PWM_OUT_L: JP1.1, R48.2, R52.1
/PWM_OUT_R: JP1.3, R47.2, R51.1
/RP2350A/FLASH_SS: R25.2, R38.2, U5.1 (~CS)
/RP2350A/QSPI_SCLK: U3.56 (QSPI_SCLK), U4.6 (SCLK), U5.6 (CLK)
/RP2350A/QSPI_SD0: U3.57 (QSPI_SD0), U4.5 (SI/SIO), U5.5 (DI(IO0))
/RP2350A/QSPI_SD1: U3.59 (QSPI_SD1), U4.2 (SO/SIO), U5.2 (DO(IO1))
/RP2350A/QSPI_SD2: U3.58 (QSPI_SD2), U4.3 (SIO2), U5.3 (IO2)
/RP2350A/QSPI_SD3: U3.55 (QSPI_SD3), U4.7 (SIO3), U5.7 (IO3)
/RP2350A/QSPI_SS: R24.1, R25.1, U3.60 (QSPI_SS)
/RP2350A/VREG_AVDD: C21.1, R20.2, U3.46 (VREG_AVDD)
/RP2350A/VREG_LX: L1.2, U3.48 (VREG_LX)
/RP2350A/XIN: U3.21 (XIN), Y1.3 (OUT)
/RP2350A/~USB_BOOT: R24.2, S2.2
/RUN: S1.1, U3.26 (RUN)
/SD Card/DAT1: J9.P8 (DAT1), J10.8 (DAT1)
/SD Card/DAT2: J9.P1 (DAT2), J10.1 (DAT2)
/TDA_OUT_L: JP1.5, R54.2, U6.6 (A_LEFT)
/TDA_OUT_R: JP1.7, R53.1, U6.8 (A_RIGHT)
/USB_D1+: R55.1, U7.8 (DP3)
/USB_D1-: R56.1, U7.7 (DM3)
/USB_D2+: R57.1, U7.6 (DP2)
/USB_D2-: R58.1, U7.5 (DM2)
/USB_D3+: J5.6 (DP1), J5.8 (DP2), JP2.1 (A), U7.4 (DP1)
/USB_D3-: J5.5 (DN2), J5.7 (DN1), JP3.1 (A), U7.3 (DM1)
GND: C1.2, C2.2, C3.1, C4.1, C9.2, C10.2, C11.2, C12.2, C13.2, C14.2, C15.2, C16.2, C17.2, C18.2, C19.2, C20.2, C21.2, C22.2, C23.2, C24.2, C25.2, C26.2, C27.1, C28.2, C29.1, C30.2, C31.2, C32.2, C33.2, C34.2, C35.2, C37.2, C38.2, C39.2, D1.2 (A), D2.2 (A), D3.2 (A), D4.2 (A), D5.2 (A), D6.2 (A), J1.8, J2.2, J2.4, J3.S, J4.S, J5.1 (GND), J5.12 (GND), J6.4 (GND1), J6.8 (GND2), J6.9 (Shield), J7.3, J8.2 (G_D2), J8.5 (G_D1), J8.8 (G_D0), J8.11 (G_CLK), J8.17 (G_DDC/CEC), J8.20 (SHIELD1), J8.21 (SHIELD2), J8.22 (SHIELD3), J8.23 (SHIELD4), J9.G1 (GND_1), J9.G2 (GND_2), J9.G3 (GND_3), J9.P6 (VSS), J10.6 (VSS), LD1.1 (K), LD2.1 (K), Q1.2 (E), Q2.2 (E), R1.1, R3.1, R4.2, R5.2, R6.2, R10.1, R43.1, R44.1, R51.2, R52.2, R53.2, R54.1, R63.2, S1.2, S2.1, U1.1 (GND), U2.4 (V-), U3.47 (VREG_PGND), U3.61 (GND), U4.4 (VSS), U5.4 (GND), U6.4 (AGND), U7.15 (GND), U7.16 (GND), Y1.2 (GND)
GPIO25: R26.2, U3.37 (GPIO25)
unnamed: C5.2, R39.2
unnamed: C6.1, R40.1, U2.7
unnamed: C7.2, R41.2
unnamed: C8.1, R42.1, U2.1
unnamed: C30.1, R45.2, R47.1, R50.1
unnamed: C31.1, R46.2, R48.1, R49.1
unnamed: C36.1, J4.T, R63.1
unnamed: C36.2, R62.1
unnamed: D7.2 (A), Q2.3 (C), R59.2, R61.1
unnamed: D7.1 (K), Q2.1 (B), R62.2
unnamed: J5.4 (CC1), R1.2
unnamed: J5.10 (CC2), R3.2
unnamed: J5.13 (SHIELD), R4.1
unnamed: J6.3 (D1+), R55.2
unnamed: J6.2 (D1-), R56.2
unnamed: J6.7 (D2+), R57.2
unnamed: J6.6 (D2-), R58.2
unnamed: J7.2, R11.2, R14.1
unnamed: J7.6, R12.2, R13.1
unnamed: J8.12 (CLKN), R27.1
unnamed: J8.10 (CLKP), R28.1
unnamed: J8.9 (D0N), R29.1
unnamed: J8.7 (D0P), R30.1
unnamed: J8.6 (D1N), R31.1
unnamed: J8.4 (D1P), R32.1
unnamed: J8.3 (D2N), R33.1
unnamed: J8.1 (D2P), R34.1
unnamed: LD1.2 (A), R2.1
unnamed: LD2.2 (A), R26.1
unnamed: Q1.1 (B), R61.2
unnamed: R5.1, R7.2
unnamed: R6.1, R8.2
unnamed: C29.2, R9.1, R44.2, U2.3 (+), U2.5 (+)
unnamed: R41.1, R42.2, U2.2 (-)
unnamed: R39.1, R40.2, U2.6 (-)
unnamed: R22.2, R23.2, U3.51 (USB_DM)
unnamed: R19.2, R21.2, U3.52 (USB_DP)
unnamed: C32.1, U6.7 (FLT)
unnamed: U7.12 (VD33), U7.14 (VD3)
VBUS: C1.1, C3.2, C4.2, C9.1, C26.1, C28.1, C33.1, C34.1, C37.1, C38.1, C39.1, J1.6, J2.1, J5.2 (VBUS), J5.11 (VBUS), J6.1 (VBUS1), J6.5 (VBUS2), J7.4, J8.18 (+5V), R9.2, R11.1, R12.1, R15.1, R18.1, U1.3 (VI), U2.8 (V+), U6.5 (VA), U7.13 (VDD5)
